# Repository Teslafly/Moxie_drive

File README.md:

# ABANDONED Moxie_drive
A motor drive based off https://github.com/vedderb/bldc-hardware capable of 75v and 100a continuous for silly electric vehicles

MoxiE-Drive - high power  motor controller
=============

design:
12-60v
120-150 continuous phase amps
based off the vesc 6. has phase shunts

Forged from the remminants of the oppressed vesc 6.
Raised on a diet of endless sphere and equals zero posts.
destined for a fight to the death in hilariously brutal Power Wheels Racing Series.
I give to you, the MoxiE-Drive.

This the Hardware for my derivitive of the Vesc-project.

## Schematic top level

## Layout -made with KiCad!-

## 3D views

Have a look at this post for a tutorial on how to get started:
http://vedder.se/2015/01/vesc-open-source-esc/

Made with KiCad 5

wonderfulfailure.wordpress.com

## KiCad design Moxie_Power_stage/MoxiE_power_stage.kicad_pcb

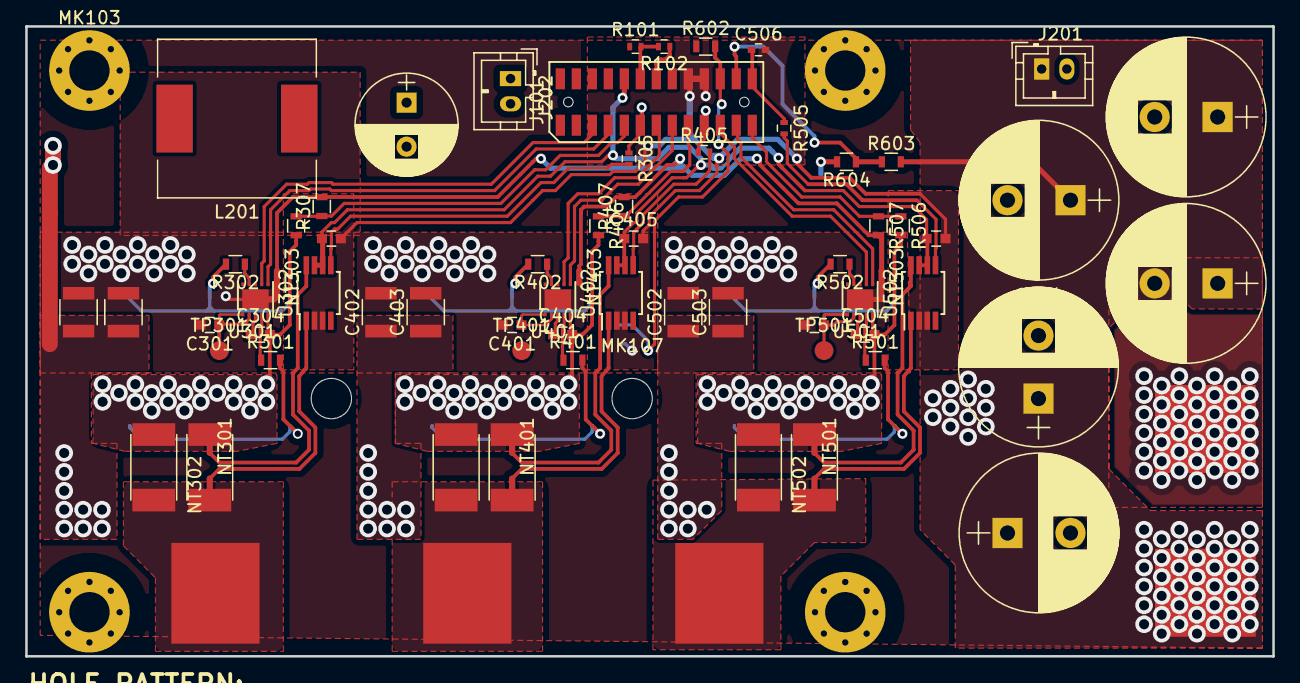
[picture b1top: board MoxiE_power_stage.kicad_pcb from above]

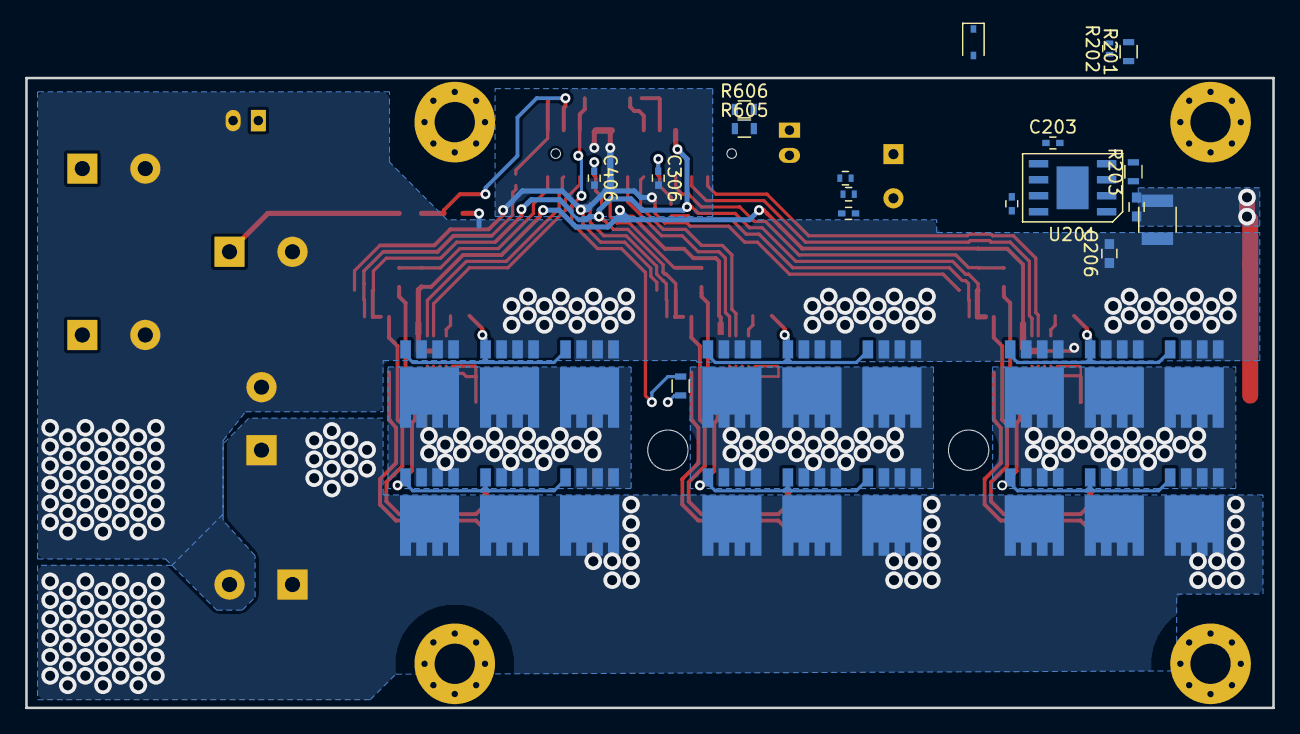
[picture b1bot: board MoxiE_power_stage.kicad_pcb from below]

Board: 2 copper layers, 99.0 x 50.0 mm, 117 parts (36 on the bottom side), 59 nets.

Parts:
C101, C102, C103, C104, C105: 470uf 80v; CP_Radial_D12.5mm_P5.00mm
C201: 2.2uF_100V; C_1210
C202: 0.1uf_100V; C_0603
C203, C204: 0.1uf; C_0402
C205: 4.7nf; C_0402
C206, C301, C304, C401, C404, C501, C504: 1uf; C_0603
C207: 100uf 25v; CP_Radial_D8.0mm_P3.50mm
C302, C303, C402, C403, C502, C503: 100v_2.2uF; C_1210
C305, C405, C505: 2.2uf; C_0603
C306, C406, C506: C; C_0402
D201: 100v 200ma; D_SOD-323
J101: Conn_02x13_Counter_Clockwise; FLE-113-01-G-DV
J201, J202: Conn_01x02; JST_PH_B2B-PH-K_02x2.00mm_Straight
L201: 100uh 2.5A; L_12x12mm_h8mm
MK101, MK102, MK103, MK104: Mounting_Hole; MountingHole_3.2mm_M3_Pad_Via
MK106, MK107: Mounting_Hole; MountingHole_3.2mm_M3
NT301, NT302, NT303, NT401, NT402, NT403, NT501, NT502, NT503: Net-Tie_2; NetTie-2_SMD_Pad0.5mm
P101, P102, P105: PHASE_3; large_wire_pad
P103: PHASE_1; large_wire_pad
P104: PHASE_2; large_wire_pad
Q301, Q302, Q303, Q304, Q305, Q306, Q401, Q402, Q403, Q404, Q405, Q406, Q501, Q502, Q503, Q504, Q505, Q506: TPH2R608NH,L1Q; SOP8_Advance
R101: 100k; R_0402
R102: 1k; R_0402
R201: 100k; R_0603
R202: 10k; R_0402
R203: 2MΩ; R_0603
R204: 20k; R_0402
R205: 2.2k; R_0402
R301, R302, R401, R402, R501, R502: 10R; R_0603
R303, R304, R403, R404, R503, R504: 300u-Ohm; R_2512_shunt_vishay
R305, R405, R505: 0; R_0402
R306, R406, R506, R603, R605: 39k; R_0603
R307, R407, R507, R604, R606: 2k2; R_0603
R601: 10k ntc; R_0603
R602: 10k; R_0603
TP301, TP401, TP501: Test_Point; Measurement_Point_Round-SMD-Pad_Small
U201: SY8502; SO8-E
U301, U401, U501: MIC4605-1YMT; TDFN2525-10ld
U302, U402, U502: AD8418; MSOP-8_3x3mm_Pitch0.65mm

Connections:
12v_buck_vout: C205.1, C206.1, C207.1, C301.1, C401.1, C501.1, D201.2, J101.25, J101.26, J202.1, L201.1, R204.1, R605.2, TP301.1, TP401.1, TP501.1, U301.1, U301.2, U401.1, U401.2, U501.1, U501.2
/12vbuck_SENSE: J101.23, R605.1, R606.1
/ADC_VBUS: J101.15, R603.1, R604.1
/EN_GATE: J101.21, R101.2, R102.2
/FAULT: J101.20, R102.1
/FAULT_RESET: C305.1, C405.1, C505.1, J101.22, R602.1, U302.6, U302.7, U402.6, U402.7, U502.6, U502.7
/FET_TEMP_SENSE: J101.16, R601.2, R602.2
/H1: J101.4, U301.6
/H2: J101.8, U401.6
/H3: J101.12, U501.6
/L1: J101.3, U301.7
/L2: J101.7, U401.7
/L3: J101.11, U501.7
/PHASE_CURRENT_1_ADC: C306.1, J101.6, R305.1
/PHASE_CURRENT_2_ADC: C406.1, J101.10, R405.1
/PHASE_CURRENT_3_ADC: C506.1, J101.14, R505.1
/PHASE_V_1_ADC: J101.5, R306.1, R307.1
/PHASE_V_2_ADC: J101.9, R406.1, R407.1
/PHASE_V_3_ADC: J101.13, R506.1, R507.1
/Vbus_to_12v/BK_BST: C204.1, U201.7
/Vbus_to_12v/buck_fb: C205.2, R204.2, R205.1, U201.5
/Vbus_to_12v/buck_sw: C204.2, L201.2, U201.8
/Vbus_to_12v/enable: R201.2, R202.1, U201.3
/phaseA/HG: R301.1, U301.4
/phaseA/HG_R: Q301.2, Q303.2, Q305.2, R301.2
/phaseA/LG: R302.1, U301.9
/phaseA/LG_R: Q302.2, Q304.2, Q306.2, R302.2
/phaseA/PHASE_I_R: R305.2, U302.5
/phaseA/PHASE_OUT: NT302.1, P103.1, R303.1, R304.1
/phaseA/PHASE_R: C304.2, NT301.1, Q301.3, Q302.1, Q303.3, Q304.1, Q305.3, Q306.1, R303.2, R304.2, R306.2, U301.5
/phaseB/HG: R401.1, U401.4
/phaseB/HG_R: Q401.2, Q403.2, Q405.2, R401.2
/phaseB/LG: R402.1, U401.9
/phaseB/LG_R: Q402.2, Q404.2, Q406.2, R402.2
/phaseB/PHASE_I_R: R405.2, U402.5
/phaseB/PHASE_OUT: NT402.1, P104.1, R403.1, R404.1
/phaseB/PHASE_R: C404.2, NT401.1, Q401.3, Q402.1, Q403.3, Q404.1, Q405.3, Q406.1, R403.2, R404.2, R406.2, U401.5
/phaseC/HG: R501.1, U501.4
/phaseC/HG_R: Q501.2, Q503.2, Q505.2, R501.2
/phaseC/LG: R502.1, U501.9
/phaseC/LG_R: Q502.2, Q504.2, Q506.2, R502.2
/phaseC/PHASE_I_R: R505.2, U502.5
/phaseC/PHASE_OUT: NT502.1, P105.1, R503.1, R504.1
/phaseC/PHASE_R: C504.2, NT501.1, Q501.3, Q502.1, Q503.3, Q504.1, Q505.3, Q506.1, R503.2, R504.2, R506.2, U501.5
GND: J101.1, J101.2, NT303.1, NT403.1, NT503.1, R101.1, R307.2, R407.2, R507.2, R606.2
GNDA: C305.2, C306.2, C405.2, C406.2, C505.2, C506.2, J101.17, J101.18, R601.1, U302.2, U302.3, U402.2, U402.3, U502.2, U502.3
GNDPWR: C101.2, C102.2, C103.2, C104.2, C105.2, C201.2, C202.2, C203.2, C206.2, C207.2, C301.2, C302.2, C303.2, C401.2, C402.2, C403.2, C501.2, C502.2, C503.2, J201.2, J202.2, NT303.2, NT403.2, NT503.2, P102.1, Q302.3, Q304.3, Q306.3, Q402.3, Q404.3, Q406.3, Q502.3, Q504.3, Q506.3, R202.2, R205.2, R604.2, U201.9, U301.8, U301.11, U401.8, U401.11, U501.8, U501.11
unnamed: C203.1, D201.1, U201.6
unnamed: C304.1, U301.3
unnamed: C404.1, U401.3
unnamed: C504.1, U501.3
unnamed: NT301.2, U302.8
unnamed: NT302.2, U302.1
unnamed: NT401.2, U402.8
unnamed: NT402.2, U402.1
unnamed: NT501.2, U502.8
unnamed: NT502.2, U502.1
unnamed: R203.2, U201.4
VBUS: C101.1, C102.1, C103.1, C104.1, C105.1, C201.1, C202.1, C302.1, C303.1, C402.1, C403.1, C502.1, C503.1, J201.1, P101.1, Q301.1, Q303.1, Q305.1, Q401.1, Q403.1, Q405.1, Q501.1, Q503.1, Q505.1, R201.1, R203.1, R603.2, U201.2

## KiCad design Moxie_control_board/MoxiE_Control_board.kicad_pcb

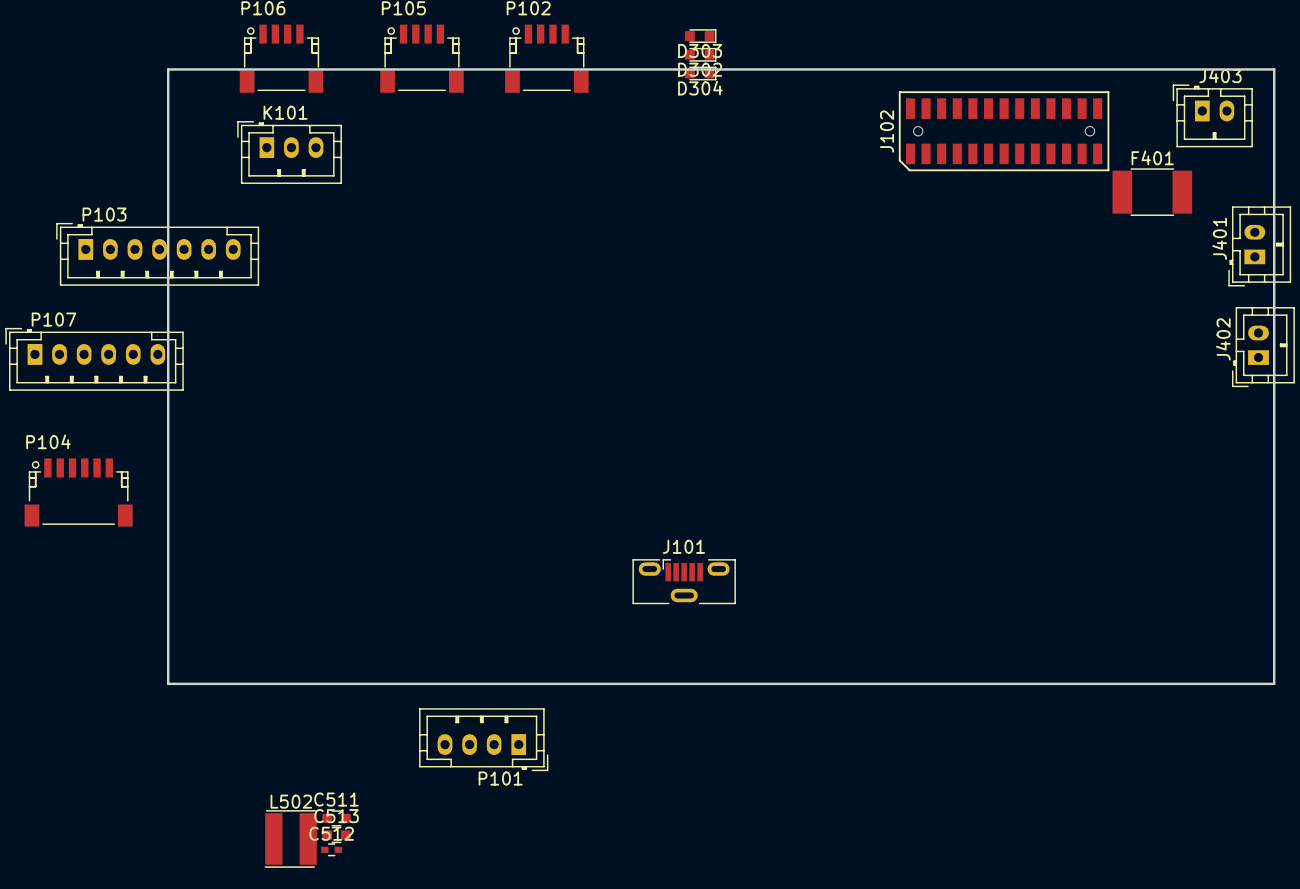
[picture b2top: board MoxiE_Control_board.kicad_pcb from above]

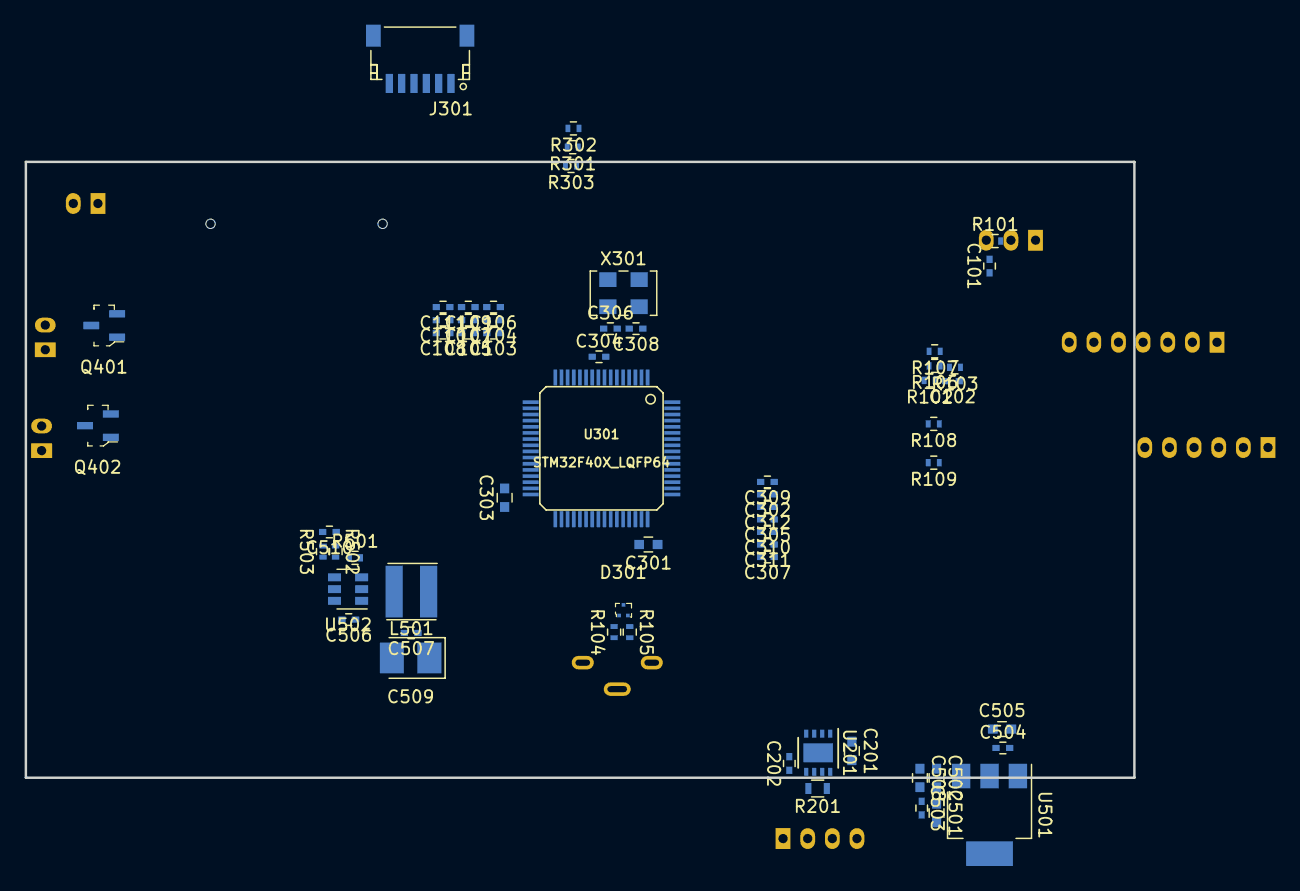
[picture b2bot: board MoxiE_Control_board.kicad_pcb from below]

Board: 2 copper layers, 90.0 x 50.0 mm, 82 parts (61 on the bottom side), 62 nets, no tracks yet.

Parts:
C101, C110, C304: 100n; C_0402
C102, C106, C107, C108, C109, C111, C202, C503, C506, C507: 100nf; C_0402
C103, C104, C105: 4.7nf; C_0402
C201, C301, C303, C502, C511: 2.2u; C_0603
C302, C305, C307, C309, C310, C311, C312, C504, C512: 2.2u; C_0402
C306, C308: 15p; C_0402
C501, C508: 2.2uf; C_0603
C505, C513: 10u; C_0603
C509: 100uf; CP_Tantalum_Case-B_EIA-3528-21_Reflow
C510: NP; C_0402
D301: TPD2EUSB30DRTR; SOT-3
D302: BLUE; LED_0603
D303: GREEN; LED_0603
D304: RED; LED_0603
F401: 0.5A polyfuse; R_1812
J101: USB_B_Micro; USB_Micro-B_Vertical_Molex-105133-0001
J102: Conn_02x14_Odd_Even; FLE-113-01-G-DV
J301: SWD; JST_SH_SM06B-SRSS-TB_06x1.00mm_Angled
J401, J402, J403: Conn_01x02; JST_PH_B2B-PH-K_02x2.00mm_Straight
K101: SERVO; JST_PH_B3B-PH-K_03x2.00mm_Straight
L501: 3.3uH; L_Bourns_SRN-4018
L502: xxuh; L_Bourns_SRN-4018
P101: CANBUS; JST_PH_B4B-PH-K_04x2.00mm_Straight
P102: Serial3; JST_SH_SM04B-SRSS-TB_04x1.00mm_Angled
P103: CTRL_SIGNALS; JST_PH_B7B-PH-K_07x2.00mm_Straight
P104: SPI; JST_SH_SM06B-SRSS-TB_06x1.00mm_Angled
P105: Serial1/tim4; JST_SH_SM04B-SRSS-TB_04x1.00mm_Angled
P106: I2C; JST_SH_SM04B-SRSS-TB_04x1.00mm_Angled
P107: HALL/Encoder; JST_PH_B6B-PH-K_06x2.00mm_Straight
Q401, Q402: IRLML6344TRPBF; SOT-23-3
R101: 100R; R_0402
R102, R103: 100k; R_0402
R104, R105: 22R; R_0402
R106, R107, R108: 2k2; R_0402
R109: 10k; R_0402
R201: 220R; R_0603
R301, R302, R303, R501: 1k; R_0402
R502: R33.2k 0.1%; R_0402
R503: 10k 0.1%; R_0402
U201: TJA1051TK-3; DFN-8-1EP_3x3mm_Pitch0.65mm
U301: STM32F40X_LQFP64; lqfp64_pad_mod
U501: AZ1117-5.0; SOT-223-3_TabPin2
U502: TPS561201; SOT-23-6
X301: 8MHz 10ppm; Oscillator_SMD_EuroQuartz_XO53-4pin_5.0x3.2mm

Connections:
+3V3: C202.1, C302.2, C305.2, C307.2, C309.2, C310.2, C311.2, C312.2, C507.1, C508.1, C509.1, C510.1, C511.1, J301.1, L501.1, L502.2, P102.3, P103.1, P104.1, P105.3, P106.3, P107.1, R106.2, R107.2, R108.2, R109.2, R301.2, R502.1, U201.5, U301.1, U301.13, U301.19, U301.32, U301.48, U301.64
+5V: C201.1, C504.1, C505.1, C512.1, C513.1, U201.3, U501.2
+12V: C501.1, C502.1, C503.1, F401.1, R501.2, U501.3, U502.3
/12vbuck_SENSE: C111.1, J102.8, U301.21
/12vgatedrive: J102.2, J102.4
/PHASE_CURRENT_1_ADC: C103.1, J102.11, U301.8
/PHASE_CURRENT_2_ADC: C104.1, J102.19, U301.9
/PHASE_CURRENT_3_ADC: C105.1, J102.26, U301.10
/PHASE_V_1_ADC: C107.1, J102.9, U301.14
/PHASE_V_2_ADC: C108.1, J102.17, U301.15
/PHASE_V_3_ADC: C109.1, J102.25, U301.16
/aux_outputs/AUX1_PWM: Q401.1, U301.22
/aux_outputs/AUX2_PWM: Q402.1, U301.23
/sheet5B3977DF/CANH: P101.3, R201.1, U201.7
/sheet5B3977DF/CANL: P101.2, R201.2, U201.6
/sheet5B3977DF/CAN_RX: U201.4, U301.61
/sheet5B3977DF/CAN_TX: U201.1, U301.62
/sheet5B3977E0/ADC_BRAKE: P103.4, R103.1, U301.27
/sheet5B3977E0/ADC_TEMP: C102.1, U301.24
/sheet5B3977E0/ADC_THROTTLE: P103.3, R102.1, U301.26
/sheet5B3977E0/ADC_VBUS: C106.1, U301.11
/sheet5B3977E0/HALL_1: P107.3, R106.1, U301.37
/sheet5B3977E0/HALL_2: P107.4, R107.1, U301.38
/sheet5B3977E0/HALL_3: P107.5, R108.1, U301.39
/sheet5B3977E0/LED_GREEN: R302.2, U301.3
/sheet5B3977E0/LED_RED: R303.2, U301.4
/sheet5B3977E0/SCL_2: P106.1, U301.29
/sheet5B3977E0/SDA_2: P106.2, U301.30
/sheet5B3977E0/SERVO: C101.2, R101.1, U301.17
/sheet5B3977E0/SPI3_MISO: P104.3, U301.56
/sheet5B3977E0/SPI3_MOSI: P104.2, U301.53
/sheet5B3977E0/SPI3_NSS: P104.5, U301.50
/sheet5B3977E0/SPI3_SCK: P104.4, U301.55
/sheet5B3977E0/TEMP_MOTOR: C110.2, P107.2, R109.1, U301.25
/sheet5B3977E0/USART1_RX: P105.1, U301.59
/sheet5B3977E0/USART1_TX: P105.2, U301.58
/sheet5B3977E0/USART3_RX: P102.1, U301.52
/sheet5B3977E0/USART3_TX: P102.2, U301.51
/sheet5B3977E0/USB_DM: D301.2, R105.1, U301.44
/sheet5B3977E0/USB_DP: D301.1, R104.1, U301.45
/sheet5B3977E0/VCAP1: C303.2, U301.31
/sheet5B3977E0/VCAP2: C301.2, U301.47
GND: C101.1, C102.2, C103.2, C104.2, C105.2, C106.2, C107.2, C108.2, C109.2, C110.1, C111.2, C201.2, C202.2, C301.1, C302.1, C303.1, C304.1, C305.1, C306.2, C307.1, C308.2, C309.1, C310.1, C311.1, C312.1, C501.2, C502.2, C503.2, C504.2, C505.2, C507.2, C508.2, C509.2, C511.2, C512.2, C513.2, D301.3, D302.2, D303.2, D304.2, J101.5, J101.6, J102.1, J102.3, J102.18, J102.20, J301.3, K101.3, P101.1, P102.4, P103.2, P103.7, P104.6, P105.4, P106.4, P107.6, R102.2, R103.2, R503.2, U201.2, U201.8, U201.9, U301.12, U301.18, U301.60, U301.63, U501.1, U502.1, X301.3
GNDPWR: J403.2, Q401.2, Q402.2
NRST: C304.2, J301.5, U301.7
unnamed: C306.1, U301.5, X301.1
unnamed: C308.1, U301.6, X301.2
unnamed: C506.1, L501.2, U502.2
unnamed: C506.2, U502.6
unnamed: C510.2, R502.2, R503.1, U502.4
unnamed: D302.1, R301.1
unnamed: D303.1, R302.1
unnamed: D304.1, R303.1
unnamed: F401.2, J401.1, J402.1, J403.1
unnamed: J101.2, R105.2
unnamed: J101.3, R104.2
unnamed: J401.2, Q401.3
unnamed: J402.2, Q402.3
unnamed: K101.1, R101.2
unnamed: R501.1, U502.5
SWCLK: J301.2, U301.49
SWDIO: J301.4, U301.46

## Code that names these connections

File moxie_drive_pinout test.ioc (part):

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Mcu.Name=STM32F405RGTx
Mcu.Package=LQFP64
Mcu.UserName=STM32F405RGTx
PA0-WKUP.Signal=ADCx_IN0
PA1.Signal=ADCx_IN1
PA10.Signal=S_TIM1_CH3
PA11.Mode=Device_Only
PA11.Signal=USB_OTG_FS_DM
PA12.Mode=Device_Only
PA12.Signal=USB_OTG_FS_DP
PA13.Signal=SYS_JTMS-SWDIO
PA14.Signal=SYS_JTCK-SWCLK
PA2.Signal=ADCx_IN2
PA3.Signal=S_TIM5_CH4
PA4.Signal=COMP_DAC1_group
PA5.Signal=COMP_DAC2_group
PA6.Signal=S_TIM13_CH1
PA7.Signal=S_TIM14_CH1
PA8.Signal=S_TIM1_CH1
PA9.Signal=S_TIM1_CH2
PB0.Signal=ADCx_IN8
PB1.Signal=ADCx_IN9
PB10.Mode=I2C
PB10.Signal=I2C2_SCL
PB11.Mode=I2C
PB11.Signal=I2C2_SDA
PB13.Mode=Output Compare1 CH1 CH1N
PB13.Signal=TIM1_CH1N
PB14.Mode=Output Compare2 CH2 CH2N
PB14.Signal=TIM1_CH2N
PB15.Mode=Output Compare3 CH3 CH3N
PB15.Signal=TIM1_CH3N
PB3.Mode=Full_Duplex_Master
PB3.Signal=SPI3_SCK
PB4.Mode=Full_Duplex_Master
PB4.Signal=SPI3_MISO
PB6.Mode=Asynchronous
PB6.Signal=USART1_TX
PB7.Mode=Asynchronous
PB7.Signal=USART1_RX
PB8.Mode=Master
PB8.Signal=CAN1_RX
PB9.Mode=Master
PB9.Signal=CAN1_TX
PC0.Signal=ADCx_IN10
PC1.Signal=ADCx_IN11
PC10.Mode=Asynchronous
PC10.Signal=USART3_TX
PC11.Mode=Asynchronous
PC11.Signal=USART3_RX
PC12.Mode=Full_Duplex_Master
PC12.Signal=SPI3_MOSI
PC2.Signal=ADCx_IN12
PC3.Signal=ADCx_IN13
PC4.Signal=ADCx_IN14
PC5.Signal=ADCx_IN15
PC6.GPIOParameters=GPIO_PuPd
PC6.GPIO_PuPd=GPIO_PULLUP
PC6.Signal=GPIO_Input
PC7.Signal=GPIO_Input
PC8.Signal=GPIO_Input
PC9.Mode=Clock-out-2
PC9.Signal=RCC_MCO_2
RCC.HSE_VALUE=25000000
RCC.SYSCLKFreq_VALUE=120000000.00000001
RCC.SYSCLKSource=RCC_SYSCLKSOURCE_PLLCLK

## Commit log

2019-08-03 initial commit of the full power moxie drive
2019-08-03 attempt at a 2 layer power stage pcb with some caveats. unfinished
2023-07-28 Update README.md
    mark as abandoned
